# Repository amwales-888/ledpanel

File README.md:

# ledpanel
32x32 LED panel

Using 16 8x8 1.9mm LED modules to make a larger 32x32 8cm panel.
Adding shift registers and a small py32 microcontroller to multiplex the display.
The panel is broken out into two boards, the first a simple breakout and the
second is a plugin board that holds the mcu and shift registers. The panel
design does not overhang any edges so multiple panels can be connected together.

<table>
  <tr>
    <td> </td>
    <td> </td>
  </tr>
  <tr>
    <td> </td>
    <td> </td>
  </tr>
</table>

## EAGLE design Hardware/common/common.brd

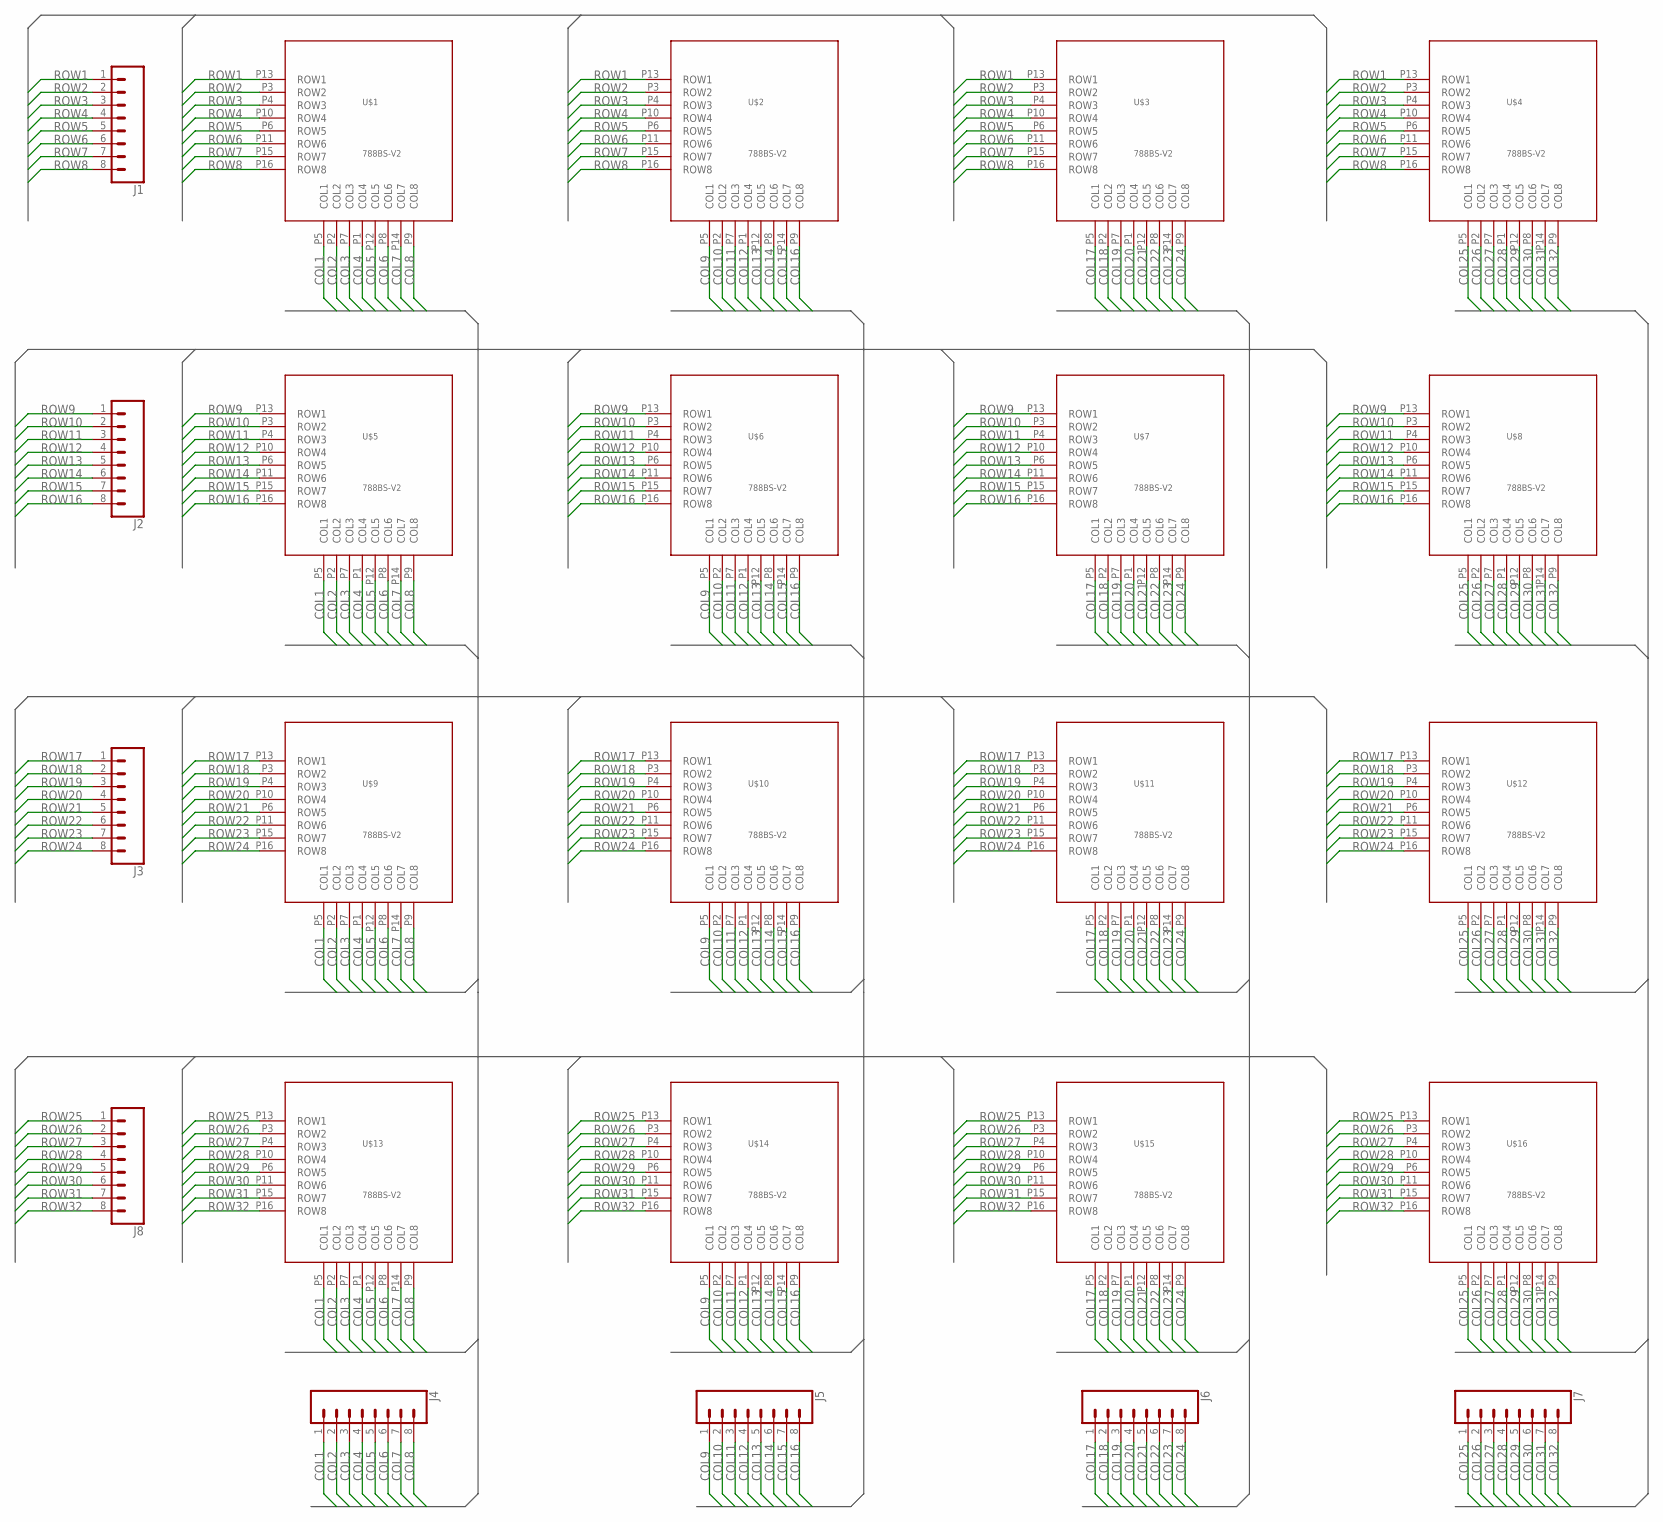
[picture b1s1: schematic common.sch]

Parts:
J1, J2, J3, J4, J5, J6, J7, J8: CONN_08"; 1X08
U$1, U$2, U$3, U$4, U$5, U$6, U$7, U$8, U$9, U$10, U$11, U$12, U$13, U$14, U$15, U$16: 788BS-V2; 788BS8X81.9MM-V2

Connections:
COL1: J4.1, U$1.P5 (COL1), U$5.P5 (COL1), U$9.P5 (COL1), U$13.P5 (COL1)
COL2: J4.2, U$1.P2 (COL2), U$5.P2 (COL2), U$9.P2 (COL2), U$13.P2 (COL2)
COL3: J4.3, U$1.P7 (COL3), U$5.P7 (COL3), U$9.P7 (COL3), U$13.P7 (COL3)
COL4: J4.4, U$1.P1 (COL4), U$5.P1 (COL4), U$9.P1 (COL4), U$13.P1 (COL4)
COL5: J4.5, U$1.P12 (COL5), U$5.P12 (COL5), U$9.P12 (COL5), U$13.P12 (COL5)
COL6: J4.6, U$1.P8 (COL6), U$5.P8 (COL6), U$9.P8 (COL6), U$13.P8 (COL6)
COL7: J4.7, U$1.P14 (COL7), U$5.P14 (COL7), U$9.P14 (COL7), U$13.P14 (COL7)
COL8: J4.8, U$1.P9 (COL8), U$5.P9 (COL8), U$9.P9 (COL8), U$13.P9 (COL8)
COL9: J5.1, U$2.P5 (COL1), U$6.P5 (COL1), U$10.P5 (COL1), U$14.P5 (COL1)
COL10: J5.2, U$2.P2 (COL2), U$6.P2 (COL2), U$10.P2 (COL2), U$14.P2 (COL2)
COL11: J5.3, U$2.P7 (COL3), U$6.P7 (COL3), U$10.P7 (COL3), U$14.P7 (COL3)
COL12: J5.4, U$2.P1 (COL4), U$6.P1 (COL4), U$10.P1 (COL4), U$14.P1 (COL4)
COL13: J5.5, U$2.P12 (COL5), U$6.P12 (COL5), U$10.P12 (COL5), U$14.P12 (COL5)
COL14: J5.6, U$2.P8 (COL6), U$6.P8 (COL6), U$10.P8 (COL6), U$14.P8 (COL6)
COL15: J5.7, U$2.P14 (COL7), U$6.P14 (COL7), U$10.P14 (COL7), U$14.P14 (COL7)
COL16: J5.8, U$2.P9 (COL8), U$6.P9 (COL8), U$10.P9 (COL8), U$14.P9 (COL8)
COL17: J6.1, U$3.P5 (COL1), U$7.P5 (COL1), U$11.P5 (COL1), U$15.P5 (COL1)
COL18: J6.2, U$3.P2 (COL2), U$7.P2 (COL2), U$11.P2 (COL2), U$15.P2 (COL2)
COL19: J6.3, U$3.P7 (COL3), U$7.P7 (COL3), U$11.P7 (COL3), U$15.P7 (COL3)
COL20: J6.4, U$3.P1 (COL4), U$7.P1 (COL4), U$11.P1 (COL4), U$15.P1 (COL4)
COL21: J6.5, U$3.P12 (COL5), U$7.P12 (COL5), U$11.P12 (COL5), U$15.P12 (COL5)
COL22: J6.6, U$3.P8 (COL6), U$7.P8 (COL6), U$11.P8 (COL6), U$15.P8 (COL6)
COL23: J6.7, U$3.P14 (COL7), U$7.P14 (COL7), U$11.P14 (COL7), U$15.P14 (COL7)
COL24: J6.8, U$3.P9 (COL8), U$7.P9 (COL8), U$11.P9 (COL8), U$15.P9 (COL8)
COL25: J7.1, U$4.P5 (COL1), U$8.P5 (COL1), U$12.P5 (COL1), U$16.P5 (COL1)
COL26: J7.2, U$4.P2 (COL2), U$8.P2 (COL2), U$12.P2 (COL2), U$16.P2 (COL2)
COL27: J7.3, U$4.P7 (COL3), U$8.P7 (COL3), U$12.P7 (COL3), U$16.P7 (COL3)
COL28: J7.4, U$4.P1 (COL4), U$8.P1 (COL4), U$12.P1 (COL4), U$16.P1 (COL4)
COL29: J7.5, U$4.P12 (COL5), U$8.P12 (COL5), U$12.P12 (COL5), U$16.P12 (COL5)
COL30: J7.6, U$4.P8 (COL6), U$8.P8 (COL6), U$12.P8 (COL6), U$16.P8 (COL6)
COL31: J7.7, U$4.P14 (COL7), U$8.P14 (COL7), U$12.P14 (COL7), U$16.P14 (COL7)
COL32: J7.8, U$4.P9 (COL8), U$8.P9 (COL8), U$12.P9 (COL8), U$16.P9 (COL8)
ROW1: J1.1, U$1.P13 (ROW1), U$2.P13 (ROW1), U$3.P13 (ROW1), U$4.P13 (ROW1)
ROW2: J1.2, U$1.P3 (ROW2), U$2.P3 (ROW2), U$3.P3 (ROW2), U$4.P3 (ROW2)
ROW3: J1.3, U$1.P4 (ROW3), U$2.P4 (ROW3), U$3.P4 (ROW3), U$4.P4 (ROW3)
ROW4: J1.4, U$1.P10 (ROW4), U$2.P10 (ROW4), U$3.P10 (ROW4), U$4.P10 (ROW4)
ROW5: J1.5, U$1.P6 (ROW5), U$2.P6 (ROW5), U$3.P6 (ROW5), U$4.P6 (ROW5)
ROW6: J1.6, U$1.P11 (ROW6), U$2.P11 (ROW6), U$3.P11 (ROW6), U$4.P11 (ROW6)
ROW7: J1.7, U$1.P15 (ROW7), U$2.P15 (ROW7), U$3.P15 (ROW7), U$4.P15 (ROW7)
ROW8: J1.8, U$1.P16 (ROW8), U$2.P16 (ROW8), U$3.P16 (ROW8), U$4.P16 (ROW8)
ROW9: J2.1, U$5.P13 (ROW1), U$6.P13 (ROW1), U$7.P13 (ROW1), U$8.P13 (ROW1)
ROW10: J2.2, U$5.P3 (ROW2), U$6.P3 (ROW2), U$7.P3 (ROW2), U$8.P3 (ROW2)
ROW11: J2.3, U$5.P4 (ROW3), U$6.P4 (ROW3), U$7.P4 (ROW3), U$8.P4 (ROW3)
ROW12: J2.4, U$5.P10 (ROW4), U$6.P10 (ROW4), U$7.P10 (ROW4), U$8.P10 (ROW4)
ROW13: J2.5, U$5.P6 (ROW5), U$6.P6 (ROW5), U$7.P6 (ROW5), U$8.P6 (ROW5)
ROW14: J2.6, U$5.P11 (ROW6), U$6.P11 (ROW6), U$7.P11 (ROW6), U$8.P11 (ROW6)
ROW15: J2.7, U$5.P15 (ROW7), U$6.P15 (ROW7), U$7.P15 (ROW7), U$8.P15 (ROW7)
ROW16: J2.8, U$5.P16 (ROW8), U$6.P16 (ROW8), U$7.P16 (ROW8), U$8.P16 (ROW8)
ROW17: J3.1, U$9.P13 (ROW1), U$10.P13 (ROW1), U$11.P13 (ROW1), U$12.P13 (ROW1)
ROW18: J3.2, U$9.P3 (ROW2), U$10.P3 (ROW2), U$11.P3 (ROW2), U$12.P3 (ROW2)
ROW19: J3.3, U$9.P4 (ROW3), U$10.P4 (ROW3), U$11.P4 (ROW3), U$12.P4 (ROW3)
ROW20: J3.4, U$9.P10 (ROW4), U$10.P10 (ROW4), U$11.P10 (ROW4), U$12.P10 (ROW4)
ROW21: J3.5, U$9.P6 (ROW5), U$10.P6 (ROW5), U$11.P6 (ROW5), U$12.P6 (ROW5)
ROW22: J3.6, U$9.P11 (ROW6), U$10.P11 (ROW6), U$11.P11 (ROW6), U$12.P11 (ROW6)
ROW23: J3.7, U$9.P15 (ROW7), U$10.P15 (ROW7), U$11.P15 (ROW7), U$12.P15 (ROW7)
ROW24: J3.8, U$9.P16 (ROW8), U$10.P16 (ROW8), U$11.P16 (ROW8), U$12.P16 (ROW8)
ROW25: J8.1, U$13.P13 (ROW1), U$14.P13 (ROW1), U$15.P13 (ROW1), U$16.P13 (ROW1)
ROW26: J8.2, U$13.P3 (ROW2), U$14.P3 (ROW2), U$15.P3 (ROW2), U$16.P3 (ROW2)
ROW27: J8.3, U$13.P4 (ROW3), U$14.P4 (ROW3), U$15.P4 (ROW3), U$16.P4 (ROW3)
ROW28: J8.4, U$13.P10 (ROW4), U$14.P10 (ROW4), U$15.P10 (ROW4), U$16.P10 (ROW4)
ROW29: J8.5, U$13.P6 (ROW5), U$14.P6 (ROW5), U$15.P6 (ROW5), U$16.P6 (ROW5)
ROW30: J8.6, U$13.P11 (ROW6), U$14.P11 (ROW6), U$15.P11 (ROW6), U$16.P11 (ROW6)
ROW31: J8.7, U$13.P15 (ROW7), U$14.P15 (ROW7), U$15.P15 (ROW7), U$16.P15 (ROW7)
ROW32: J8.8, U$13.P16 (ROW8), U$14.P16 (ROW8), U$15.P16 (ROW8), U$16.P16 (ROW8)

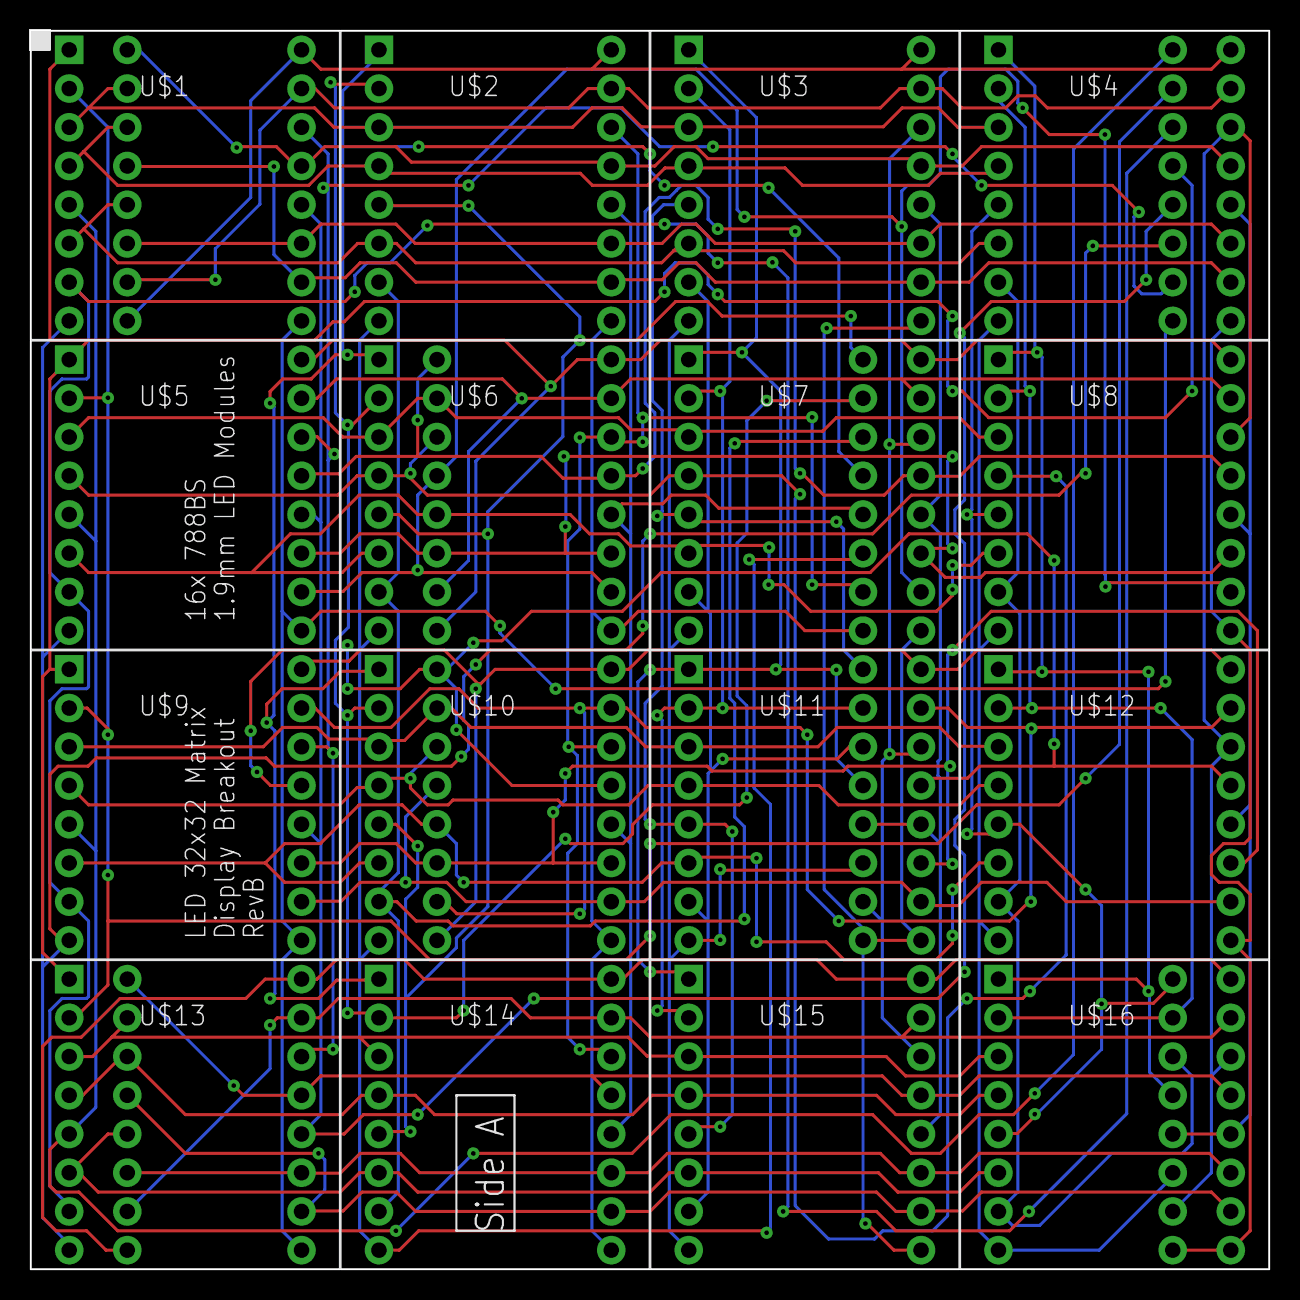
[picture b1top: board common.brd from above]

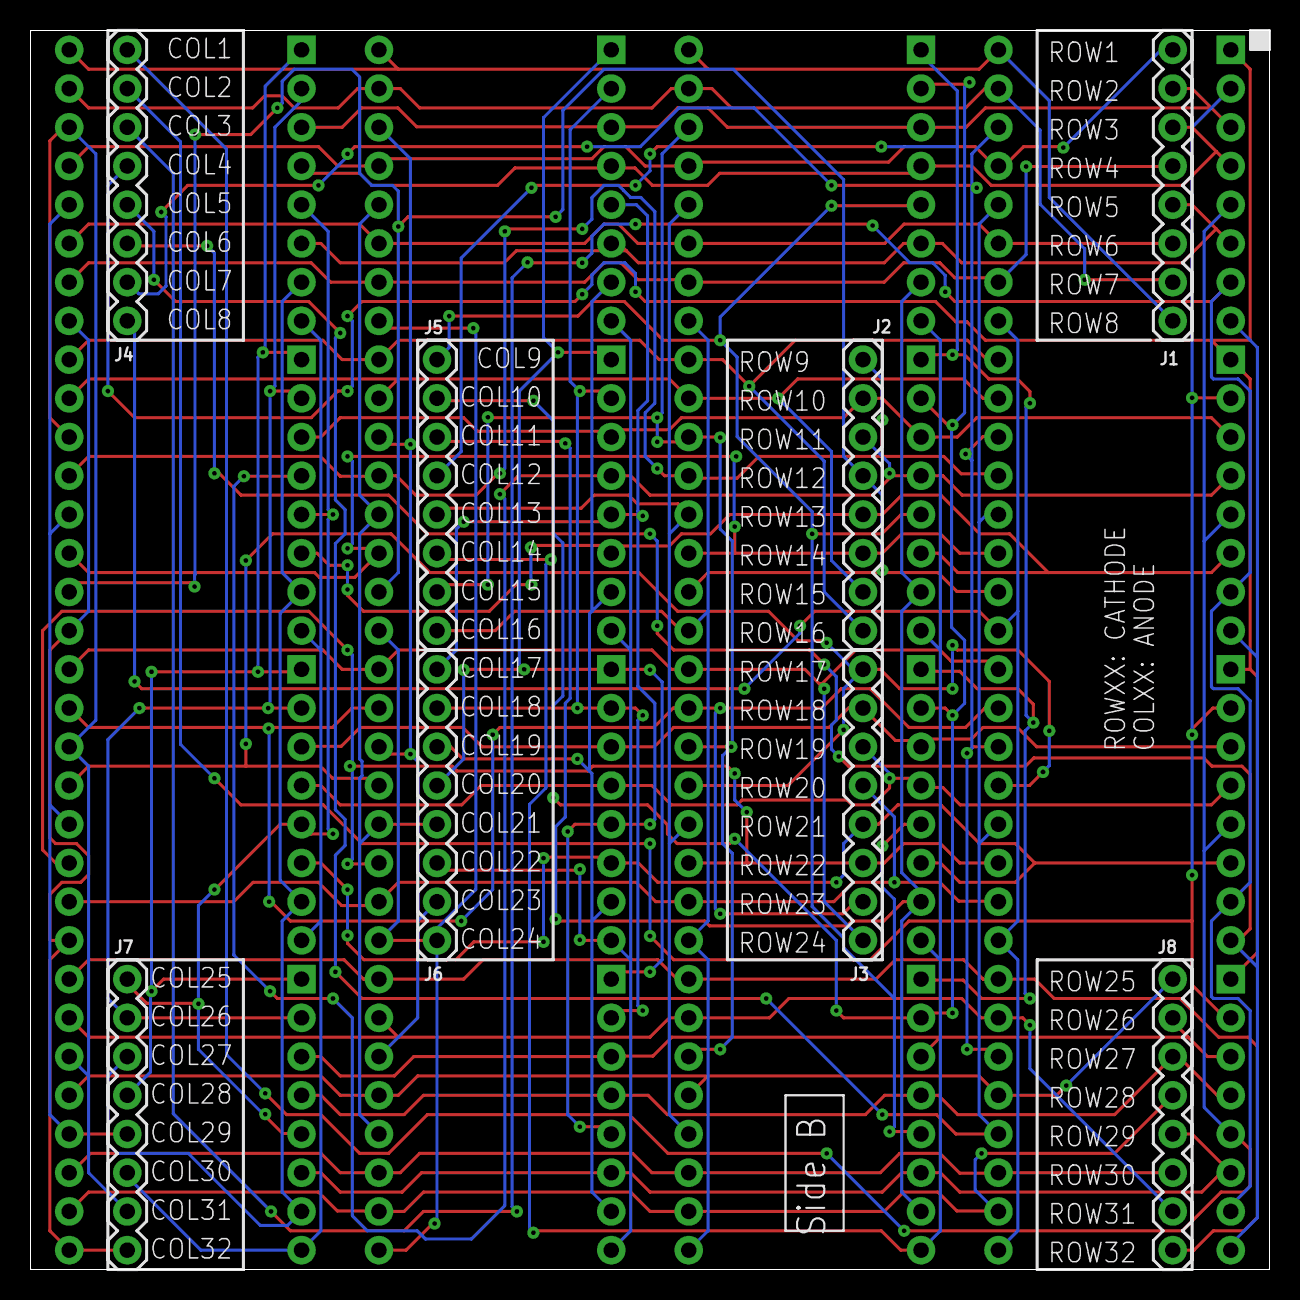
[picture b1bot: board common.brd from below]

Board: 2 copper layers, 81.3 x 81.3 mm, 24 parts (8 on the bottom side), 64 nets.

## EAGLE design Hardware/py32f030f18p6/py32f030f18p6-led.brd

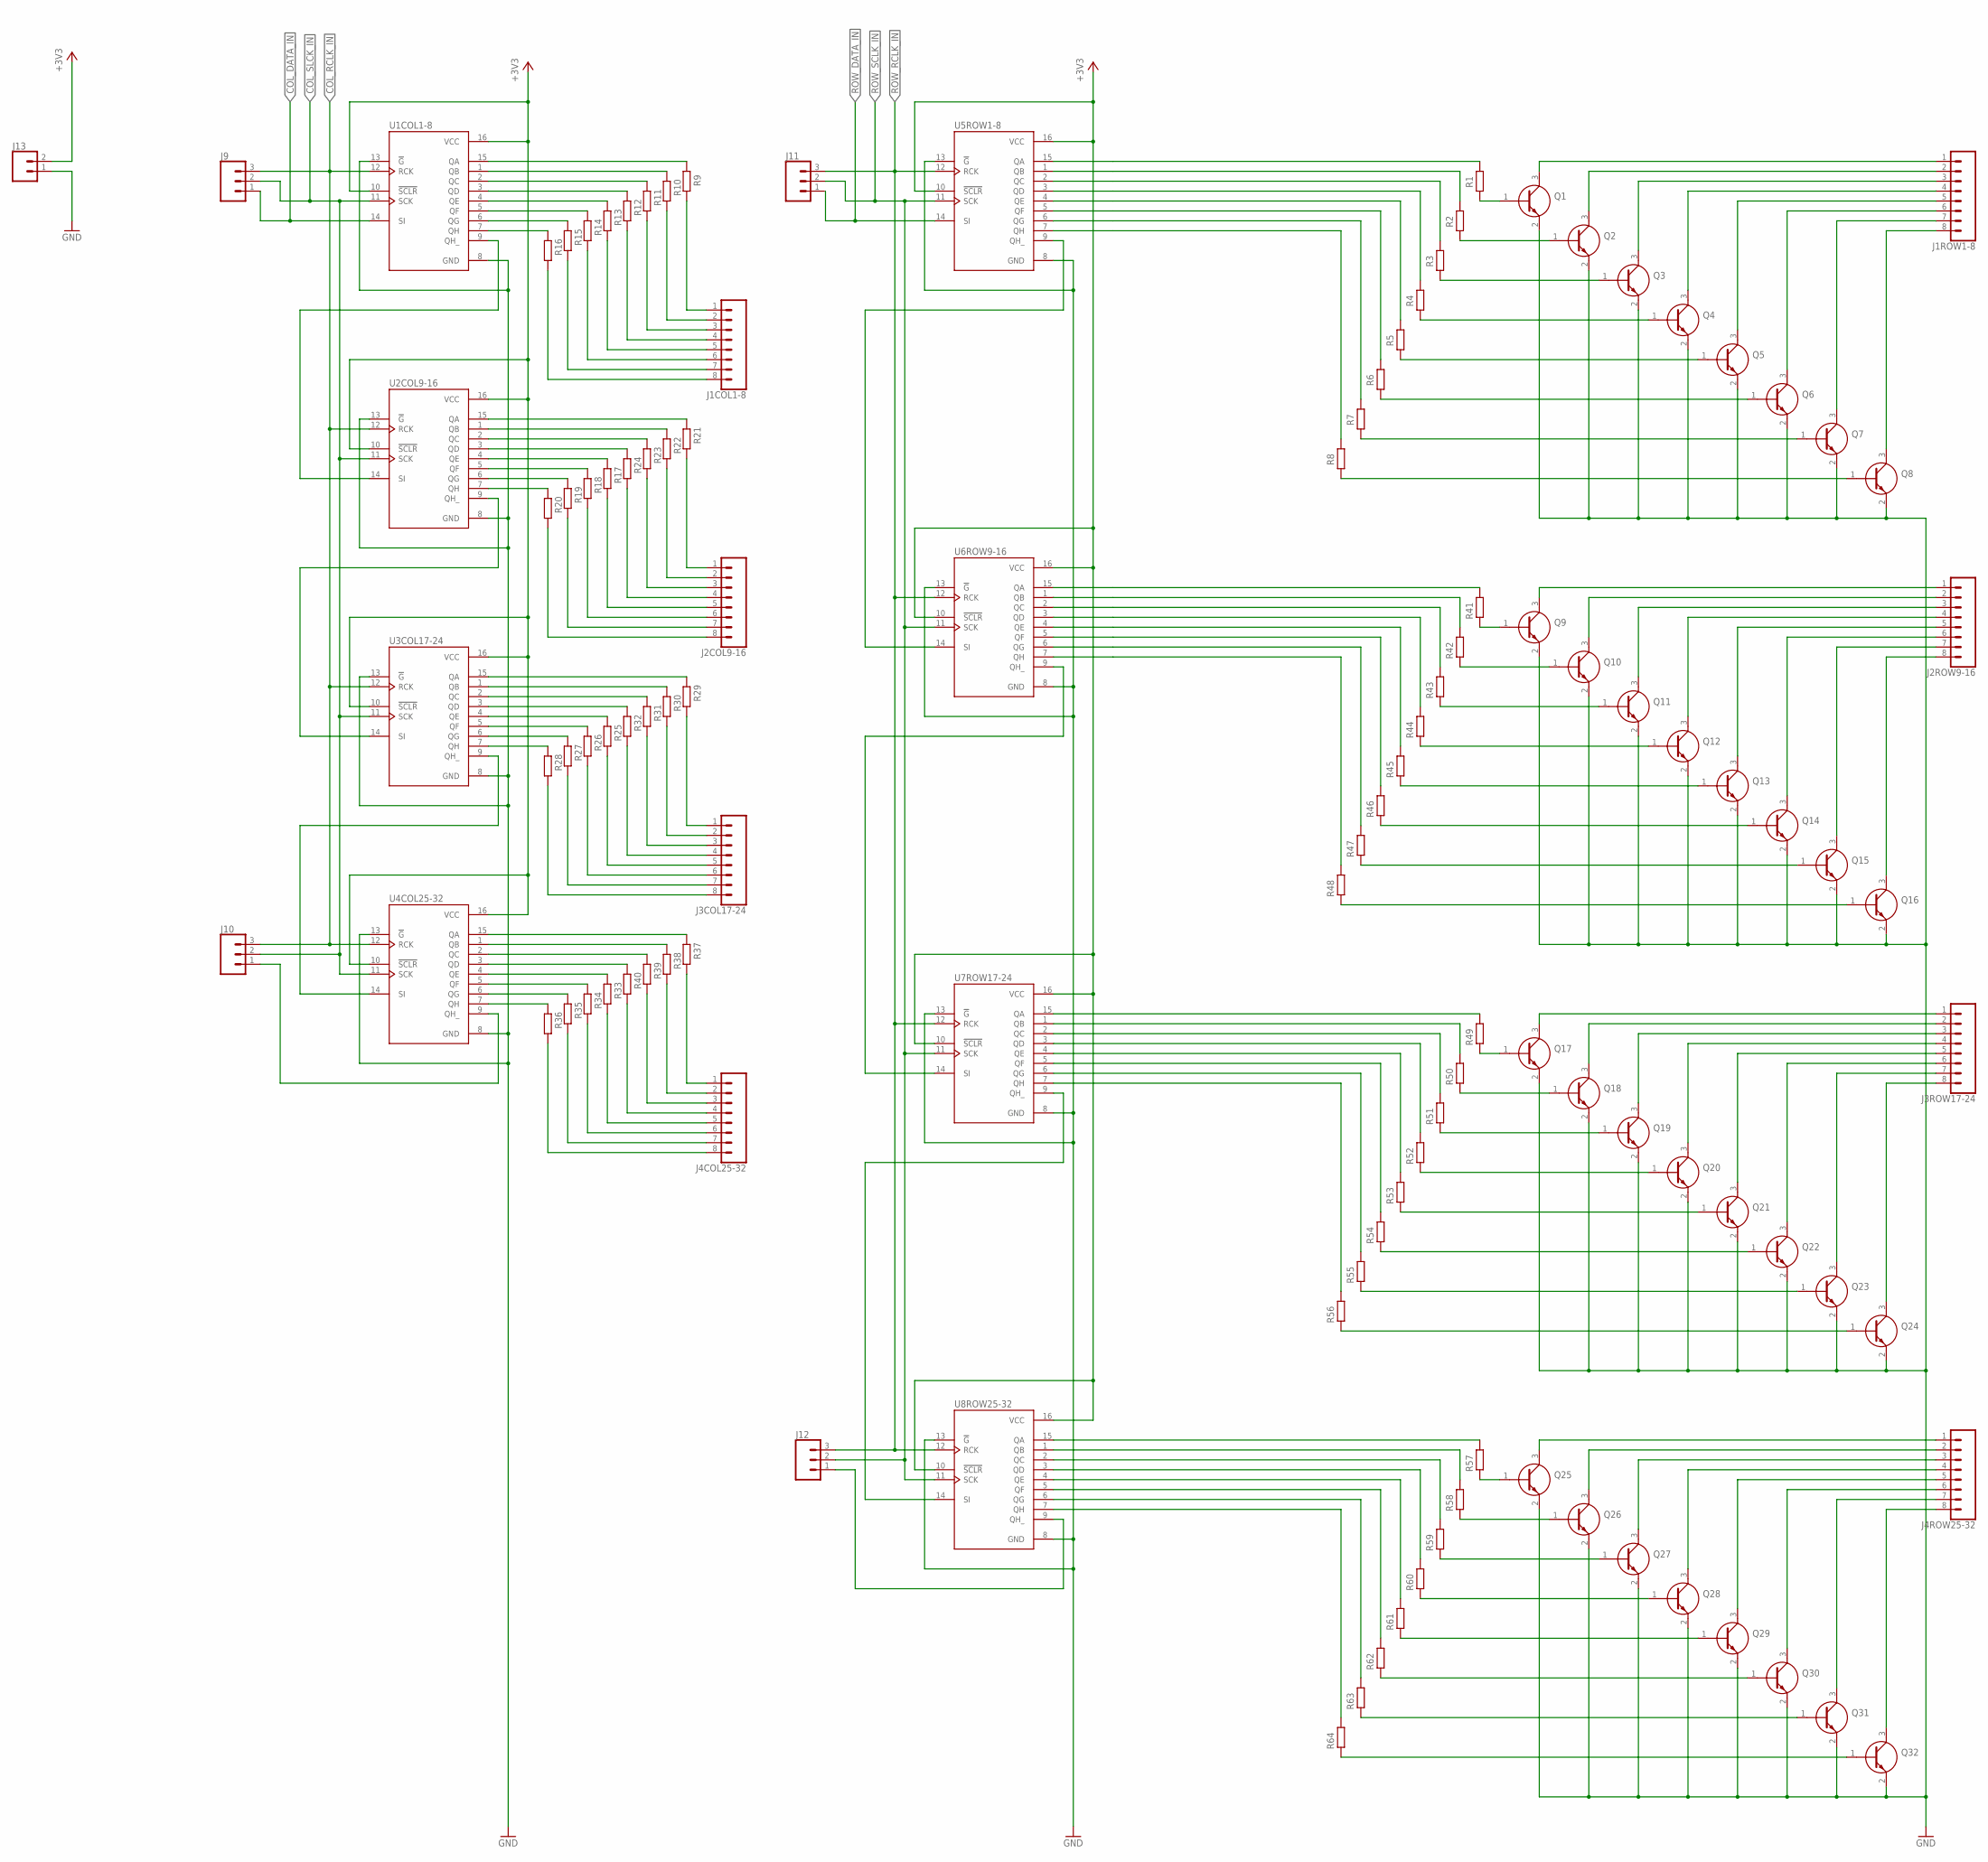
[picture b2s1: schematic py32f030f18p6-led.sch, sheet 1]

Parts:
J1COL1-8, J1ROW1-8, J2COL9-16, J2ROW9-16, J3COL17-24, J3ROW17-24, J4COL25-32, J4ROW25-32: CONN_08"; 1X08
J9, J10, J11, J12: 455-1750-1-ND; 1X03
J13: CONN_02; 1X02
Q1, Q2, Q3, Q4, Q5, Q6, Q7, Q8, Q9, Q10, Q11, Q12, Q13, Q14, Q15, Q16, Q17, Q18, Q19, Q20, Q21, Q22, Q23, Q24, Q25, Q26, Q27, Q28, Q29, Q30, Q31, Q32: MMBT3904LT3G; SOT96P237X111-3N
R1, R2, R3, R4, R5, R6, R7, R8, R9, R10, R11, R12, R13, R14, R15, R16, R17, R18, R19, R20, R21, R22, R23, R24, R25, R26, R27, R28, R29, R30, R31, R32, R33, R34, R35, R36, R37, R38, R39, R40, R41, R42, R43, R44, R45, R46, R47, R48, R49, R50, R51, R52, R53, R54, R55, R56, R57, R58, R59, R60, R61, R62, R63, R64: 10K; R0805
U1COL1-8, U2COL9-16, U3COL17-24, U4COL25-32, U5ROW1-8, U6ROW9-16, U7ROW17-24, U8ROW25-32: TC74HC595AF(EL,F); SOIC127P780X190-16N

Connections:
+3V3: J13.2, U1COL1-8.10 (!SCLR), U1COL1-8.16 (VCC), U2COL9-16.10 (!SCLR), U2COL9-16.16 (VCC), U3COL17-24.10 (!SCLR), U3COL17-24.16 (VCC), U4COL25-32.10 (!SCLR), U4COL25-32.16 (VCC), U5ROW1-8.10 (!SCLR), U5ROW1-8.16 (VCC), U6ROW9-16.10 (!SCLR), U6ROW9-16.16 (VCC), U7ROW17-24.10 (!SCLR), U7ROW17-24.16 (VCC), U8ROW25-32.10 (!SCLR), U8ROW25-32.16 (VCC); also elsewhere on the board
COL_DATA_IN: J9.1, U1COL1-8.14 (SI); also elsewhere on the board
COL_RCLK_IN: J9.3, J10.3, U1COL1-8.12 (RCK), U2COL9-16.12 (RCK), U3COL17-24.12 (RCK), U4COL25-32.12 (RCK); also elsewhere on the board
COL_SLCK_IN: J9.2, J10.2, U1COL1-8.11 (SCK), U2COL9-16.11 (SCK), U3COL17-24.11 (SCK), U4COL25-32.11 (SCK); also elsewhere on the board
GND: J13.1, Q1.2 (E), Q2.2 (E), Q3.2 (E), Q4.2 (E), Q5.2 (E), Q6.2 (E), Q7.2 (E), Q8.2 (E), Q9.2 (E), Q10.2 (E), Q11.2 (E), Q12.2 (E), Q13.2 (E), Q14.2 (E), Q15.2 (E), Q16.2 (E), Q17.2 (E), Q18.2 (E), Q19.2 (E), Q20.2 (E), Q21.2 (E), Q22.2 (E), Q23.2 (E), Q24.2 (E), Q25.2 (E), Q26.2 (E), Q27.2 (E), Q28.2 (E), Q29.2 (E), Q30.2 (E), Q31.2 (E), Q32.2 (E), U1COL1-8.8 (GND), U1COL1-8.13 (!G), U2COL9-16.8 (GND), U2COL9-16.13 (!G), U3COL17-24.8 (GND), U3COL17-24.13 (!G), U4COL25-32.8 (GND), U4COL25-32.13 (!G), U5ROW1-8.8 (GND), U5ROW1-8.13 (!G), U6ROW9-16.8 (GND), U6ROW9-16.13 (!G), U7ROW17-24.8 (GND), U7ROW17-24.13 (!G), U8ROW25-32.8 (GND), U8ROW25-32.13 (!G); also elsewhere on the board
unnamed: J1ROW1-8.1, Q1.3 (C)
unnamed: J1ROW1-8.2, Q2.3 (C)
unnamed: J1ROW1-8.3, Q3.3 (C)
unnamed: J1ROW1-8.4, Q4.3 (C)
unnamed: J1ROW1-8.5, Q5.3 (C)
unnamed: J1ROW1-8.6, Q6.3 (C)
unnamed: J1ROW1-8.7, Q7.3 (C)
unnamed: J1ROW1-8.8, Q8.3 (C)
unnamed: R13.2, U1COL1-8.4 (QE)
unnamed: Q1.1 (B), R1.2
unnamed: Q2.1 (B), R2.2
unnamed: Q3.1 (B), R3.2
unnamed: Q4.1 (B), R4.2
unnamed: Q5.1 (B), R5.2
unnamed: Q6.1 (B), R6.2
unnamed: Q7.1 (B), R7.2
unnamed: Q8.1 (B), R8.2
unnamed: R12.2, U1COL1-8.3 (QD)
unnamed: R11.2, U1COL1-8.2 (QC)
unnamed: R14.2, U1COL1-8.5 (QF)
unnamed: R16.2, U1COL1-8.7 (QH)
unnamed: R15.2, U1COL1-8.6 (QG)
unnamed: R10.2, U1COL1-8.1 (QB)
unnamed: R9.2, U1COL1-8.15 (QA)
unnamed: J1COL1-8.3, R11.1
unnamed: J1COL1-8.4, R12.1
unnamed: J1COL1-8.5, R13.1
unnamed: J1COL1-8.6, R14.1
unnamed: J1COL1-8.7, R15.1
unnamed: J1COL1-8.8, R16.1
unnamed: Q9.1 (B), R41.2
unnamed: R20.2, U2COL9-16.7 (QH)
unnamed: R19.2, U2COL9-16.6 (QG)
unnamed: J1COL1-8.2, R10.1
unnamed: R18.2, U2COL9-16.5 (QF)
unnamed: R17.2, U2COL9-16.4 (QE)
unnamed: J1COL1-8.1, R9.1
unnamed: R24.2, U2COL9-16.3 (QD)
unnamed: R23.2, U2COL9-16.2 (QC)
unnamed: R22.2, U2COL9-16.1 (QB)
unnamed: R21.2, U2COL9-16.15 (QA)
unnamed: J2COL9-16.2, R22.1
unnamed: J2COL9-16.1, R21.1
unnamed: J2COL9-16.3, R23.1
unnamed: J2COL9-16.4, R24.1
unnamed: Q10.1 (B), R42.2
unnamed: J2COL9-16.5, R17.1
unnamed: J2COL9-16.6, R18.1
unnamed: J2COL9-16.7, R19.1
unnamed: J2COL9-16.8, R20.1
unnamed: U2COL9-16.9 (QH_), U3COL17-24.14 (SI)
unnamed: U1COL1-8.9 (QH_), U2COL9-16.14 (SI)
unnamed: Q11.1 (B), R43.2
unnamed: Q12.1 (B), R44.2
unnamed: Q13.1 (B), R45.2
unnamed: R28.2, U3COL17-24.7 (QH)
unnamed: R27.2, U3COL17-24.6 (QG)
unnamed: R26.2, U3COL17-24.5 (QF)
unnamed: R25.2, U3COL17-24.4 (QE)
unnamed: R32.2, U3COL17-24.3 (QD)
unnamed: R31.2, U3COL17-24.2 (QC)
unnamed: R30.2, U3COL17-24.1 (QB)
unnamed: R29.2, U3COL17-24.15 (QA)
unnamed: J3COL17-24.2, R30.1
unnamed: J3COL17-24.1, R29.1
unnamed: J3COL17-24.3, R31.1
unnamed: J3COL17-24.4, R32.1
unnamed: J3COL17-24.5, R25.1
unnamed: J3COL17-24.6, R26.1
unnamed: J3COL17-24.7, R27.1
unnamed: J3COL17-24.8, R28.1
unnamed: U3COL17-24.9 (QH_), U4COL25-32.14 (SI)
unnamed: Q14.1 (B), R46.2
unnamed: Q15.1 (B), R47.2
unnamed: Q16.1 (B), R48.2
unnamed: R36.2, U4COL25-32.7 (QH)
unnamed: R35.2, U4COL25-32.6 (QG)
unnamed: R34.2, U4COL25-32.5 (QF)
unnamed: R33.2, U4COL25-32.4 (QE)
unnamed: R40.2, U4COL25-32.3 (QD)
unnamed: R39.2, U4COL25-32.2 (QC)
unnamed: R38.2, U4COL25-32.1 (QB)
unnamed: R37.2, U4COL25-32.15 (QA)
unnamed: J4COL25-32.2, R38.1
unnamed: J4COL25-32.1, R37.1
unnamed: J4COL25-32.3, R39.1
unnamed: J4COL25-32.4, R40.1
unnamed: J4COL25-32.5, R33.1
unnamed: J4COL25-32.6, R34.1
unnamed: J4COL25-32.7, R35.1
unnamed: J4COL25-32.8, R36.1
unnamed: J10.1, U4COL25-32.9 (QH_)
unnamed: J2ROW9-16.1, Q9.3 (C)
unnamed: J2ROW9-16.2, Q10.3 (C)
unnamed: J2ROW9-16.3, Q11.3 (C)
unnamed: J2ROW9-16.4, Q12.3 (C)
unnamed: J2ROW9-16.5, Q13.3 (C)
unnamed: J2ROW9-16.6, Q14.3 (C)
unnamed: J2ROW9-16.7, Q15.3 (C)
unnamed: J2ROW9-16.8, Q16.3 (C)
unnamed: Q17.1 (B), R49.2
unnamed: Q18.1 (B), R50.2
unnamed: Q19.1 (B), R51.2
unnamed: Q20.1 (B), R52.2
unnamed: Q21.1 (B), R53.2
unnamed: Q22.1 (B), R54.2
unnamed: Q23.1 (B), R55.2
unnamed: Q24.1 (B), R56.2
unnamed: J3ROW17-24.1, Q17.3 (C)
unnamed: J3ROW17-24.2, Q18.3 (C)
unnamed: J3ROW17-24.3, Q19.3 (C)
unnamed: J3ROW17-24.4, Q20.3 (C)
unnamed: J3ROW17-24.5, Q21.3 (C)
unnamed: J3ROW17-24.6, Q22.3 (C)
unnamed: J3ROW17-24.7, Q23.3 (C)
unnamed: J3ROW17-24.8, Q24.3 (C)
unnamed: Q25.1 (B), R57.2
unnamed: Q26.1 (B), R58.2
unnamed: Q27.1 (B), R59.2
unnamed: Q28.1 (B), R60.2
unnamed: Q29.1 (B), R61.2
unnamed: Q30.1 (B), R62.2
unnamed: Q31.1 (B), R63.2
unnamed: Q32.1 (B), R64.2
unnamed: J4ROW25-32.1, Q25.3 (C)
unnamed: J4ROW25-32.2, Q26.3 (C)
unnamed: J4ROW25-32.3, Q27.3 (C)
unnamed: J4ROW25-32.4, Q28.3 (C)
unnamed: J4ROW25-32.5, Q29.3 (C)
unnamed: J4ROW25-32.6, Q30.3 (C)
unnamed: J4ROW25-32.7, Q31.3 (C)
unnamed: J4ROW25-32.8, Q32.3 (C)
unnamed: R8.1, U5ROW1-8.7 (QH)
unnamed: R7.1, U5ROW1-8.6 (QG)
unnamed: R6.1, U5ROW1-8.5 (QF)
unnamed: R5.1, U5ROW1-8.4 (QE)
unnamed: R4.1, U5ROW1-8.3 (QD)
unnamed: R3.1, U5ROW1-8.2 (QC)
unnamed: R2.1, U5ROW1-8.1 (QB)
unnamed: R1.1, U5ROW1-8.15 (QA)
unnamed: R48.1, U6ROW9-16.7 (QH)
unnamed: R47.1, U6ROW9-16.6 (QG)
unnamed: R46.1, U6ROW9-16.5 (QF)
unnamed: R45.1, U6ROW9-16.4 (QE)
unnamed: R44.1, U6ROW9-16.3 (QD)
unnamed: R43.1, U6ROW9-16.2 (QC)
unnamed: R42.1, U6ROW9-16.1 (QB)
unnamed: R41.1, U6ROW9-16.15 (QA)
unnamed: U6ROW9-16.9 (QH_), U7ROW17-24.14 (SI)
unnamed: U5ROW1-8.9 (QH_), U6ROW9-16.14 (SI)
unnamed: R56.1, U7ROW17-24.7 (QH)
unnamed: R55.1, U7ROW17-24.6 (QG)
unnamed: R54.1, U7ROW17-24.5 (QF)
unnamed: R53.1, U7ROW17-24.4 (QE)
unnamed: R52.1, U7ROW17-24.3 (QD)
unnamed: R51.1, U7ROW17-24.2 (QC)
unnamed: R50.1, U7ROW17-24.1 (QB)
unnamed: R49.1, U7ROW17-24.15 (QA)
unnamed: U7ROW17-24.9 (QH_), U8ROW25-32.14 (SI)
unnamed: R64.1, U8ROW25-32.7 (QH)
unnamed: R63.1, U8ROW25-32.6 (QG)
unnamed: R62.1, U8ROW25-32.5 (QF)
unnamed: R61.1, U8ROW25-32.4 (QE)
unnamed: R60.1, U8ROW25-32.3 (QD)
unnamed: R59.1, U8ROW25-32.2 (QC)
unnamed: R58.1, U8ROW25-32.1 (QB)
unnamed: R57.1, U8ROW25-32.15 (QA)
unnamed: J12.1, U8ROW25-32.9 (QH_)
ROW_DATA_IN: J11.1, U5ROW1-8.14 (SI); also elsewhere on the board
ROW_RCLK_IN: J11.3, J12.3, U5ROW1-8.12 (RCK), U6ROW9-16.12 (RCK), U7ROW17-24.12 (RCK), U8ROW25-32.12 (RCK); also elsewhere on the board
ROW_SCLK_IN: J11.2, J12.2, U5ROW1-8.11 (SCK), U6ROW9-16.11 (SCK), U7ROW17-24.11 (SCK), U8ROW25-32.11 (SCK); also elsewhere on the board

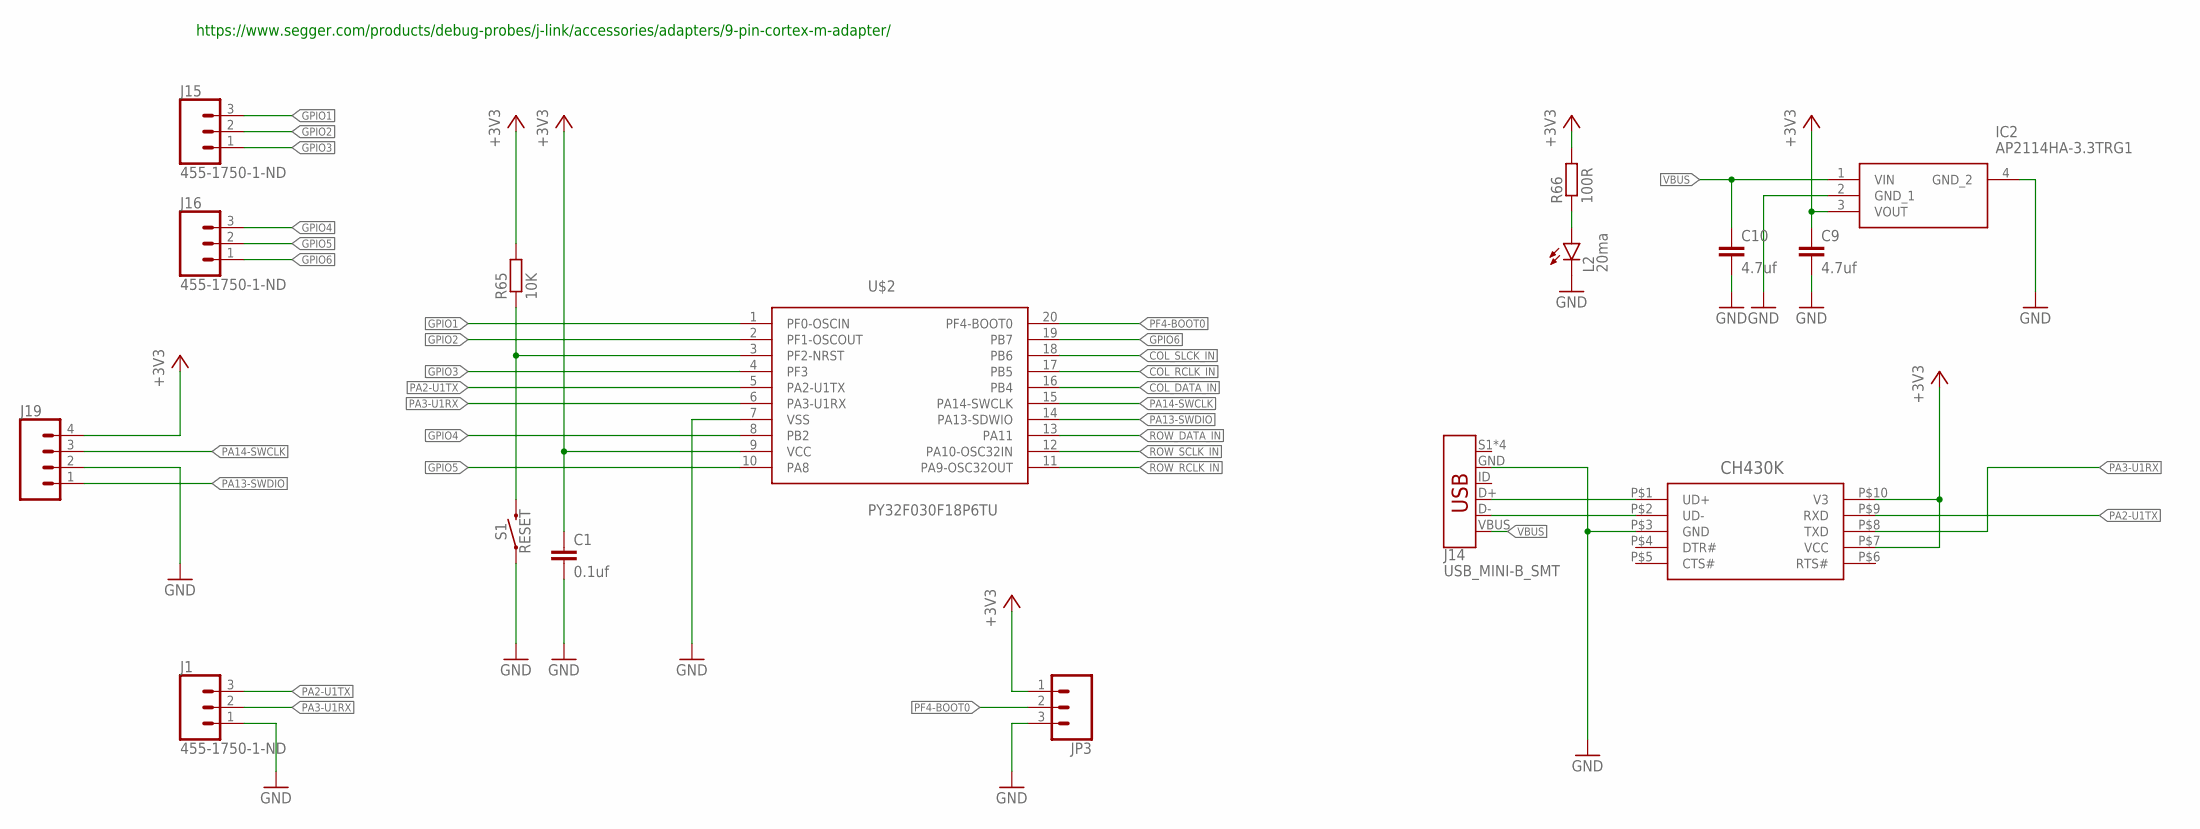
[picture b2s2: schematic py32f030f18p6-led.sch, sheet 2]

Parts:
C1: 0.1uf; C0805
C9, C10: 4.7uf; C1206
IC2: AP2114HA-3.3TRG1; SOT230P700X180-4N
J1, J15, J16: 455-1750-1-ND; 1X03
J14: USB_MINI-B_SMT; USB-MINIB
J19: CONN_04PTH; 1X04
JP3: 455-1750-1-ND; 1X03
L2: 20ma; SML0805
R65: 10K; R0805
R66: 100R; R0805
S1: RESET; TACTILE_SWITCH_SMD_6.0X3.5MM
U$1: CH430K; ESSOP-10
U$2: PY32F030F18P6TU; TSSOP20

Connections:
+3V3: C1.1, C9.1, IC2.3 (VOUT), J19.4, JP3.1, R65.2, R66.2, U$1.P$7 (VCC), U$1.P$10 (V3), U$2.9 (VCC); also elsewhere on the board
COL_DATA_IN: U$2.16 (PB4); also elsewhere on the board
COL_RCLK_IN: U$2.17 (PB5); also elsewhere on the board
COL_SLCK_IN: U$2.18 (PB6); also elsewhere on the board
GND: C1.2, C9.2, C10.2, IC2.2 (GND_1), IC2.4 (GND_2), J1.1, J14.GND, J19.2, JP3.3, L2.C, S1.1, U$1.P$3 (GND), U$2.7 (VSS); also elsewhere on the board
GPIO1: J15.3, U$2.1 (PF0-OSCIN)
GPIO2: J15.2, U$2.2 (PF1-OSCOUT)
GPIO3: J15.1, U$2.4 (PF3)
GPIO4: J16.3, U$2.8 (PB2)
GPIO5: J16.2, U$2.10 (PA8)
GPIO6: J16.1, U$2.19 (PB7)
unnamed: L2.A, R66.1
PA2-U1TX: J1.3, U$1.P$9 (RXD), U$2.5 (PA2-U1TX)
PA3-U1RX: J1.2, U$1.P$8 (TXD), U$2.6 (PA3-U1RX)
PA13-SWDIO: J19.1, U$2.14 (PA13-SDWIO)
PA14-SWCLK: J19.3, U$2.15 (PA14-SWCLK)
PF2-NRST: R65.1, S1.2, U$2.3 (PF2-NRST)
PF4-BOOT0: JP3.2, U$2.20 (PF4-BOOT0)
ROW_DATA_IN: U$2.13 (PA11); also elsewhere on the board
ROW_RCLK_IN: U$2.11 (PA9-OSC32OUT); also elsewhere on the board
ROW_SCLK_IN: U$2.12 (PA10-OSC32IN); also elsewhere on the board
USB_N: J14.D-, U$1.P$2 (UD-)
USB_P: J14.D+, U$1.P$1 (UD+)
VBUS: C10.1, IC2.1 (VIN), J14.VBUS

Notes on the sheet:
https://www.segger.com/products/debug-probes/j-link/accessories/adapters/9-pin-cortex-m-adapter/

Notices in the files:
Firmware/py32f030f18p6/User/main.c:
© Copyright (c) Puya Semiconductor Co.
All rights reserved.
© Copyright (c) 2016 STMicroelectronics.
This software component is licensed by ST under BSD 3-Clause license,
the "License"; You may not use this file except in compliance with the
License. You may obtain a copy of the License at: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
parts and their libraries:
SparkFun-Connectors: Licensing: Creative Commons ShareAlike 4.0 International - https://creativecommons.org/licenses/by-sa/4.0
